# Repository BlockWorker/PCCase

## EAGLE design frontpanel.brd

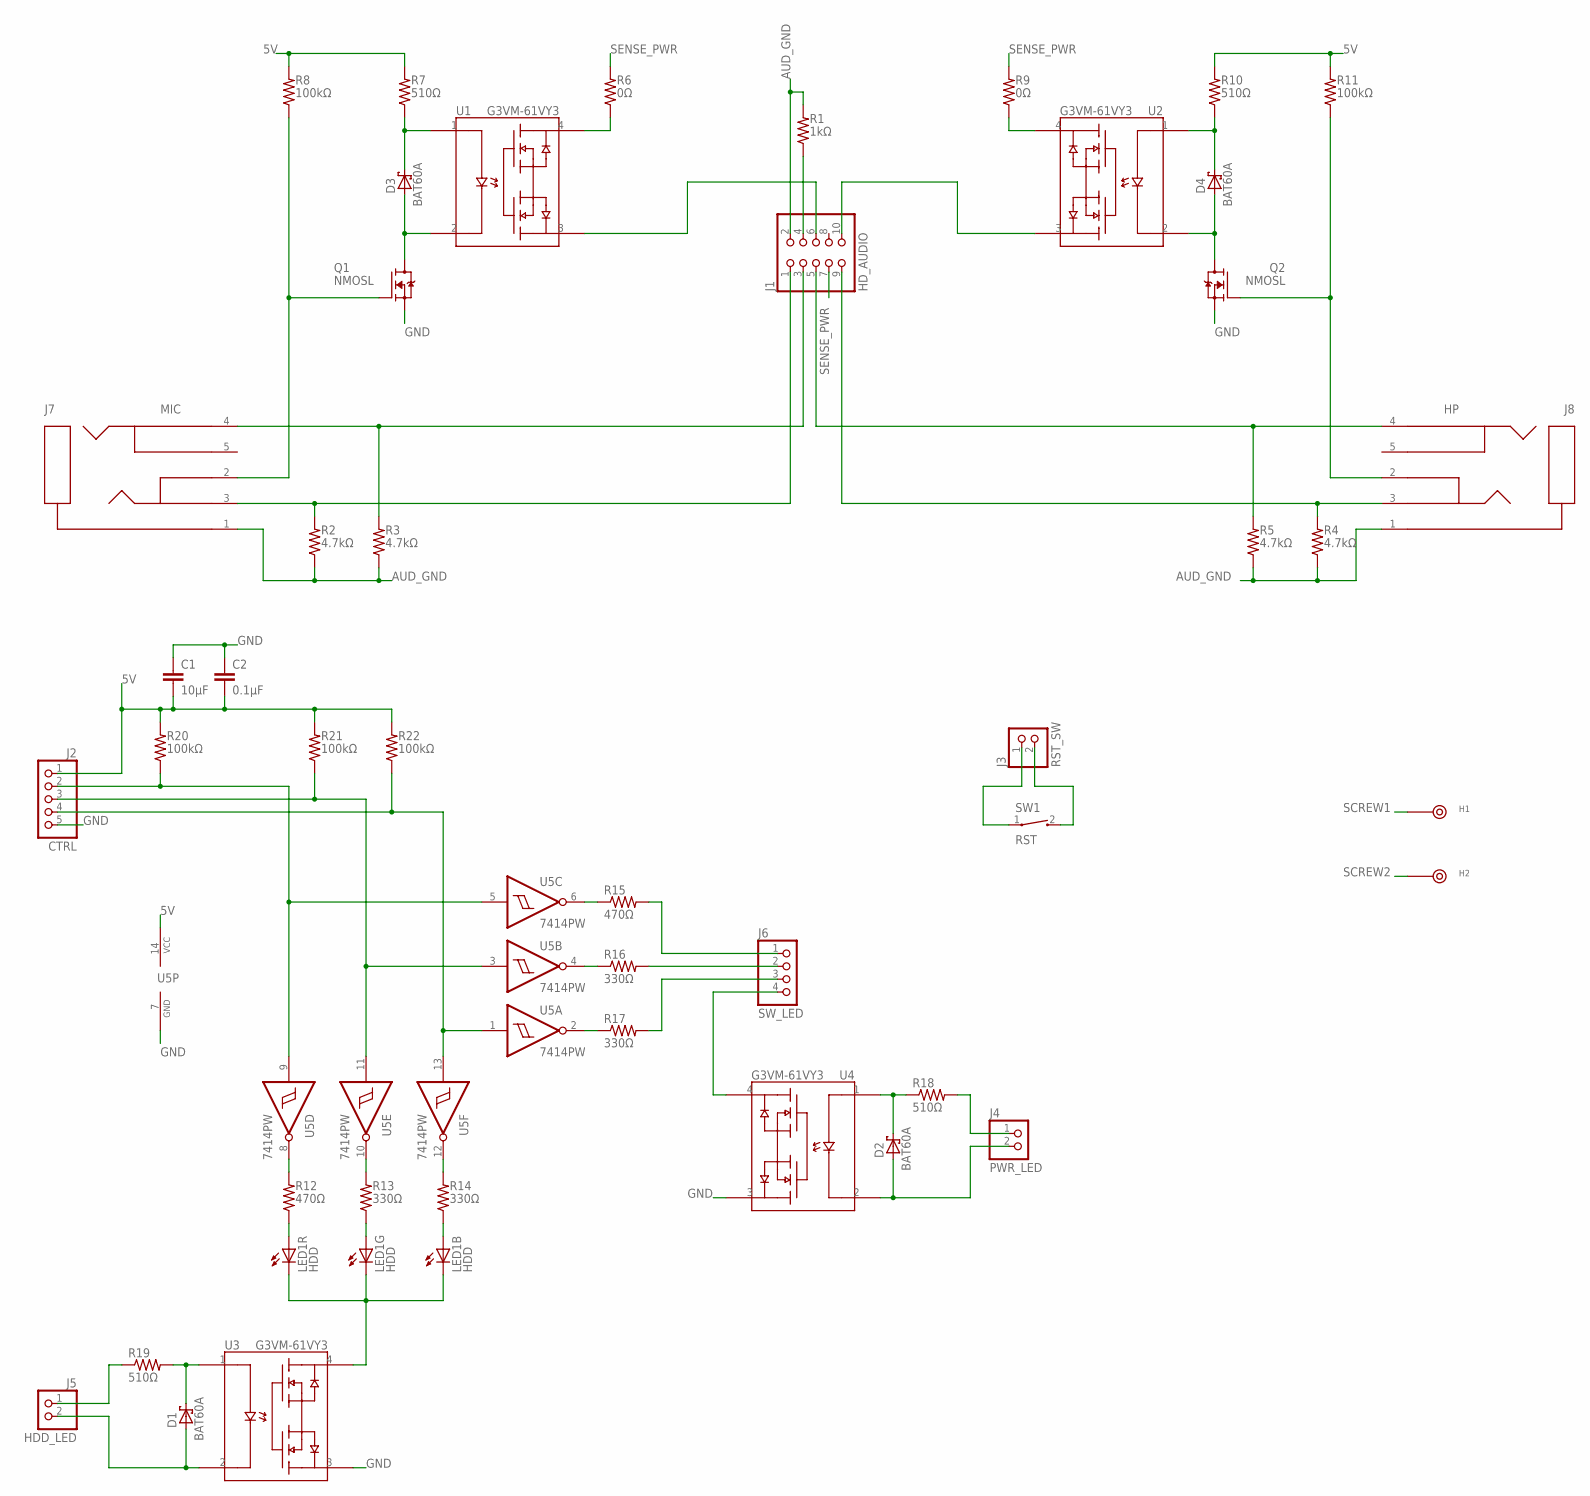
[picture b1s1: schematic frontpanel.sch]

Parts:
C1: 10µF; C0805
C2: 0.1µF; C0603
D1, D2, D3, D4: BAT60A; SOD323
H1, H2: 7466313R
J1: HD_AUDIO; 2X05
J2: CTRL; 1X05
J3: RST_SW; 1X02
J4: PWR_LED; 1X02
J5: HDD_LED; 1X02
J6: SW_LED; 1X04
J7: MIC; ACJS-MV35-5
J8: HP; ACJS-MV35-5
LED1: HDD; PLCC-6
Q1, Q2: NMOSL; SOT23
R1: 1kΩ; R0603
R2, R3, R4, R5: 4.7kΩ; R0603
R6, R9: 0Ω; R0603
R7, R10, R18, R19: 510Ω; R0603
R8, R11, R20, R21, R22: 100kΩ; R0603
R12, R15: 470Ω; R0603
R13, R14, R16, R17: 330Ω; R0603
SW1: RST; TLS-*J-LFS
U1, U2, U3, U4: G3VM-61VY3; SOP-4
U5: 7414PW; TSSOP14

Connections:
5V: C1.2, C2.2, J2.1, R7.2, R8.2, R10.2, R11.2, R20.2, R21.2, R22.2, U5.14 (VCC)
!PWM_B: J2.4, R22.1, U5.1 (I), U5.13 (I)
!PWM_G: J2.3, R21.1, U5.3 (I), U5.11 (I)
!PWM_R: J2.2, R20.1, U5.5 (I), U5.9 (I)
AUD_GND: J1.2, J7.1 (S), J8.1 (S), R1.2, R2.1, R3.1, R4.1, R5.1
GND: C1.1, C2.1, J2.5, Q1.2 (S), Q2.2 (S), U3.3 (1), U4.3 (1), U5.7 (GND)
HDD_LED_B: LED1.5 (A), R14.1
HDD_LED_B_RAW: R14.2, U5.12 (O)
HDD_LED_DRIVE: D1.1 (C), R19.2, U3.1 (A)
HDD_LED_G: LED1.3 (A), R13.1
HDD_LED_G_RAW: R13.2, U5.10 (O)
HDD_LED_IN+: J5.1, R19.1
HDD_LED_IN-: D1.2 (A), J5.2, U3.2 (K)
HDD_LED_K: LED1.2 (C), LED1.4 (C), LED1.6 (C), U3.4 (2)
HDD_LED_R: LED1.1 (A), R12.1
HDD_LED_R_RAW: R12.2, U5.8 (O)
HEADER_SENSE: J1.4, R1.1
HP_L: J1.9, J8.3 (T), R4.2
HP_R: J1.5, J8.4 (R), R5.2
HP_SENSE: J1.10, U2.3 (1)
HP_SENSEDR_A: D4.1 (C), R10.1, U2.1 (A)
HP_SENSEDR_K: D4.2 (A), Q2.3 (D), U2.2 (K)
HP_SENSE_PWR: R9.1, U2.4 (2)
HP_TIPSW: J8.2 (T-RETURN), Q2.1 (G), R11.1
MIC_L: J1.1, J7.3 (T), R2.2
MIC_R: J1.3, J7.4 (R), R3.2
MIC_SENSE: J1.6, U1.3 (1)
MIC_SENSEDR_A: D3.1 (C), R7.1, U1.1 (A)
MIC_SENSEDR_K: D3.2 (A), Q1.3 (D), U1.2 (K)
MIC_SENSE_PWR: R6.1, U1.4 (2)
MIC_TIPSW: J7.2 (T-RETURN), Q1.1 (G), R8.1
PWR_LED_IN+: J4.1, R18.2
PWR_LED_IN-: D2.2 (A), J4.2, U4.2 (K)
RST_SW_1: J3.1, SW1.1
RST_SW_2: J3.2, SW1.2
SCREW1: H1.H1, H1.H2, H1.P
SCREW2: H2.H1, H2.H2, H2.P
SENSE_PWR: J1.7, R6.2, R9.2
SW_LED_B: J6.3, R17.2
SW_LED_B_RAW: R17.1, U5.2 (O)
SW_LED_DRIVE: D2.1 (C), R18.1, U4.1 (A)
SW_LED_G: J6.2, R16.2
SW_LED_G_RAW: R16.1, U5.4 (O)
SW_LED_K: J6.4, U4.4 (2)
SW_LED_R: J6.1, R15.2
SW_LED_R_RAW: R15.1, U5.6 (O)

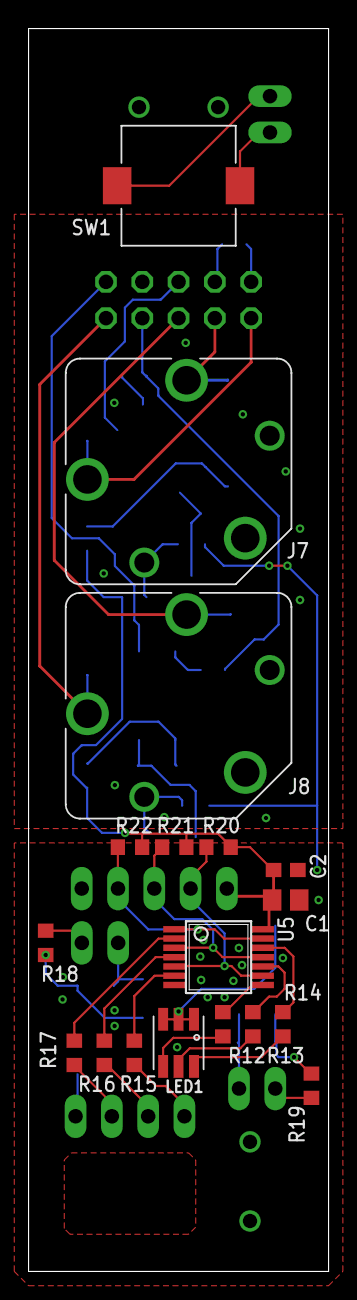
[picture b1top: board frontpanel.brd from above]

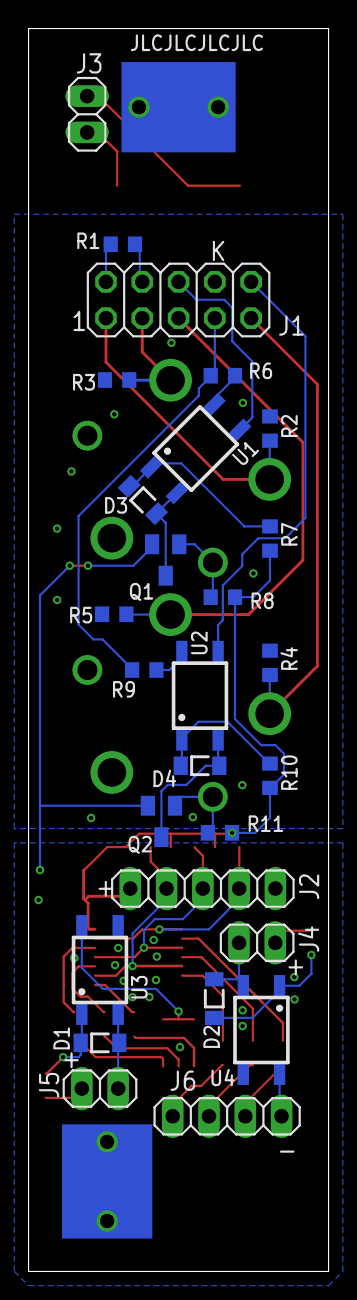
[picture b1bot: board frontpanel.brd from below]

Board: 2 copper layers, 21.0 x 87.0 mm, 47 parts (29 on the bottom side), 46 nets.

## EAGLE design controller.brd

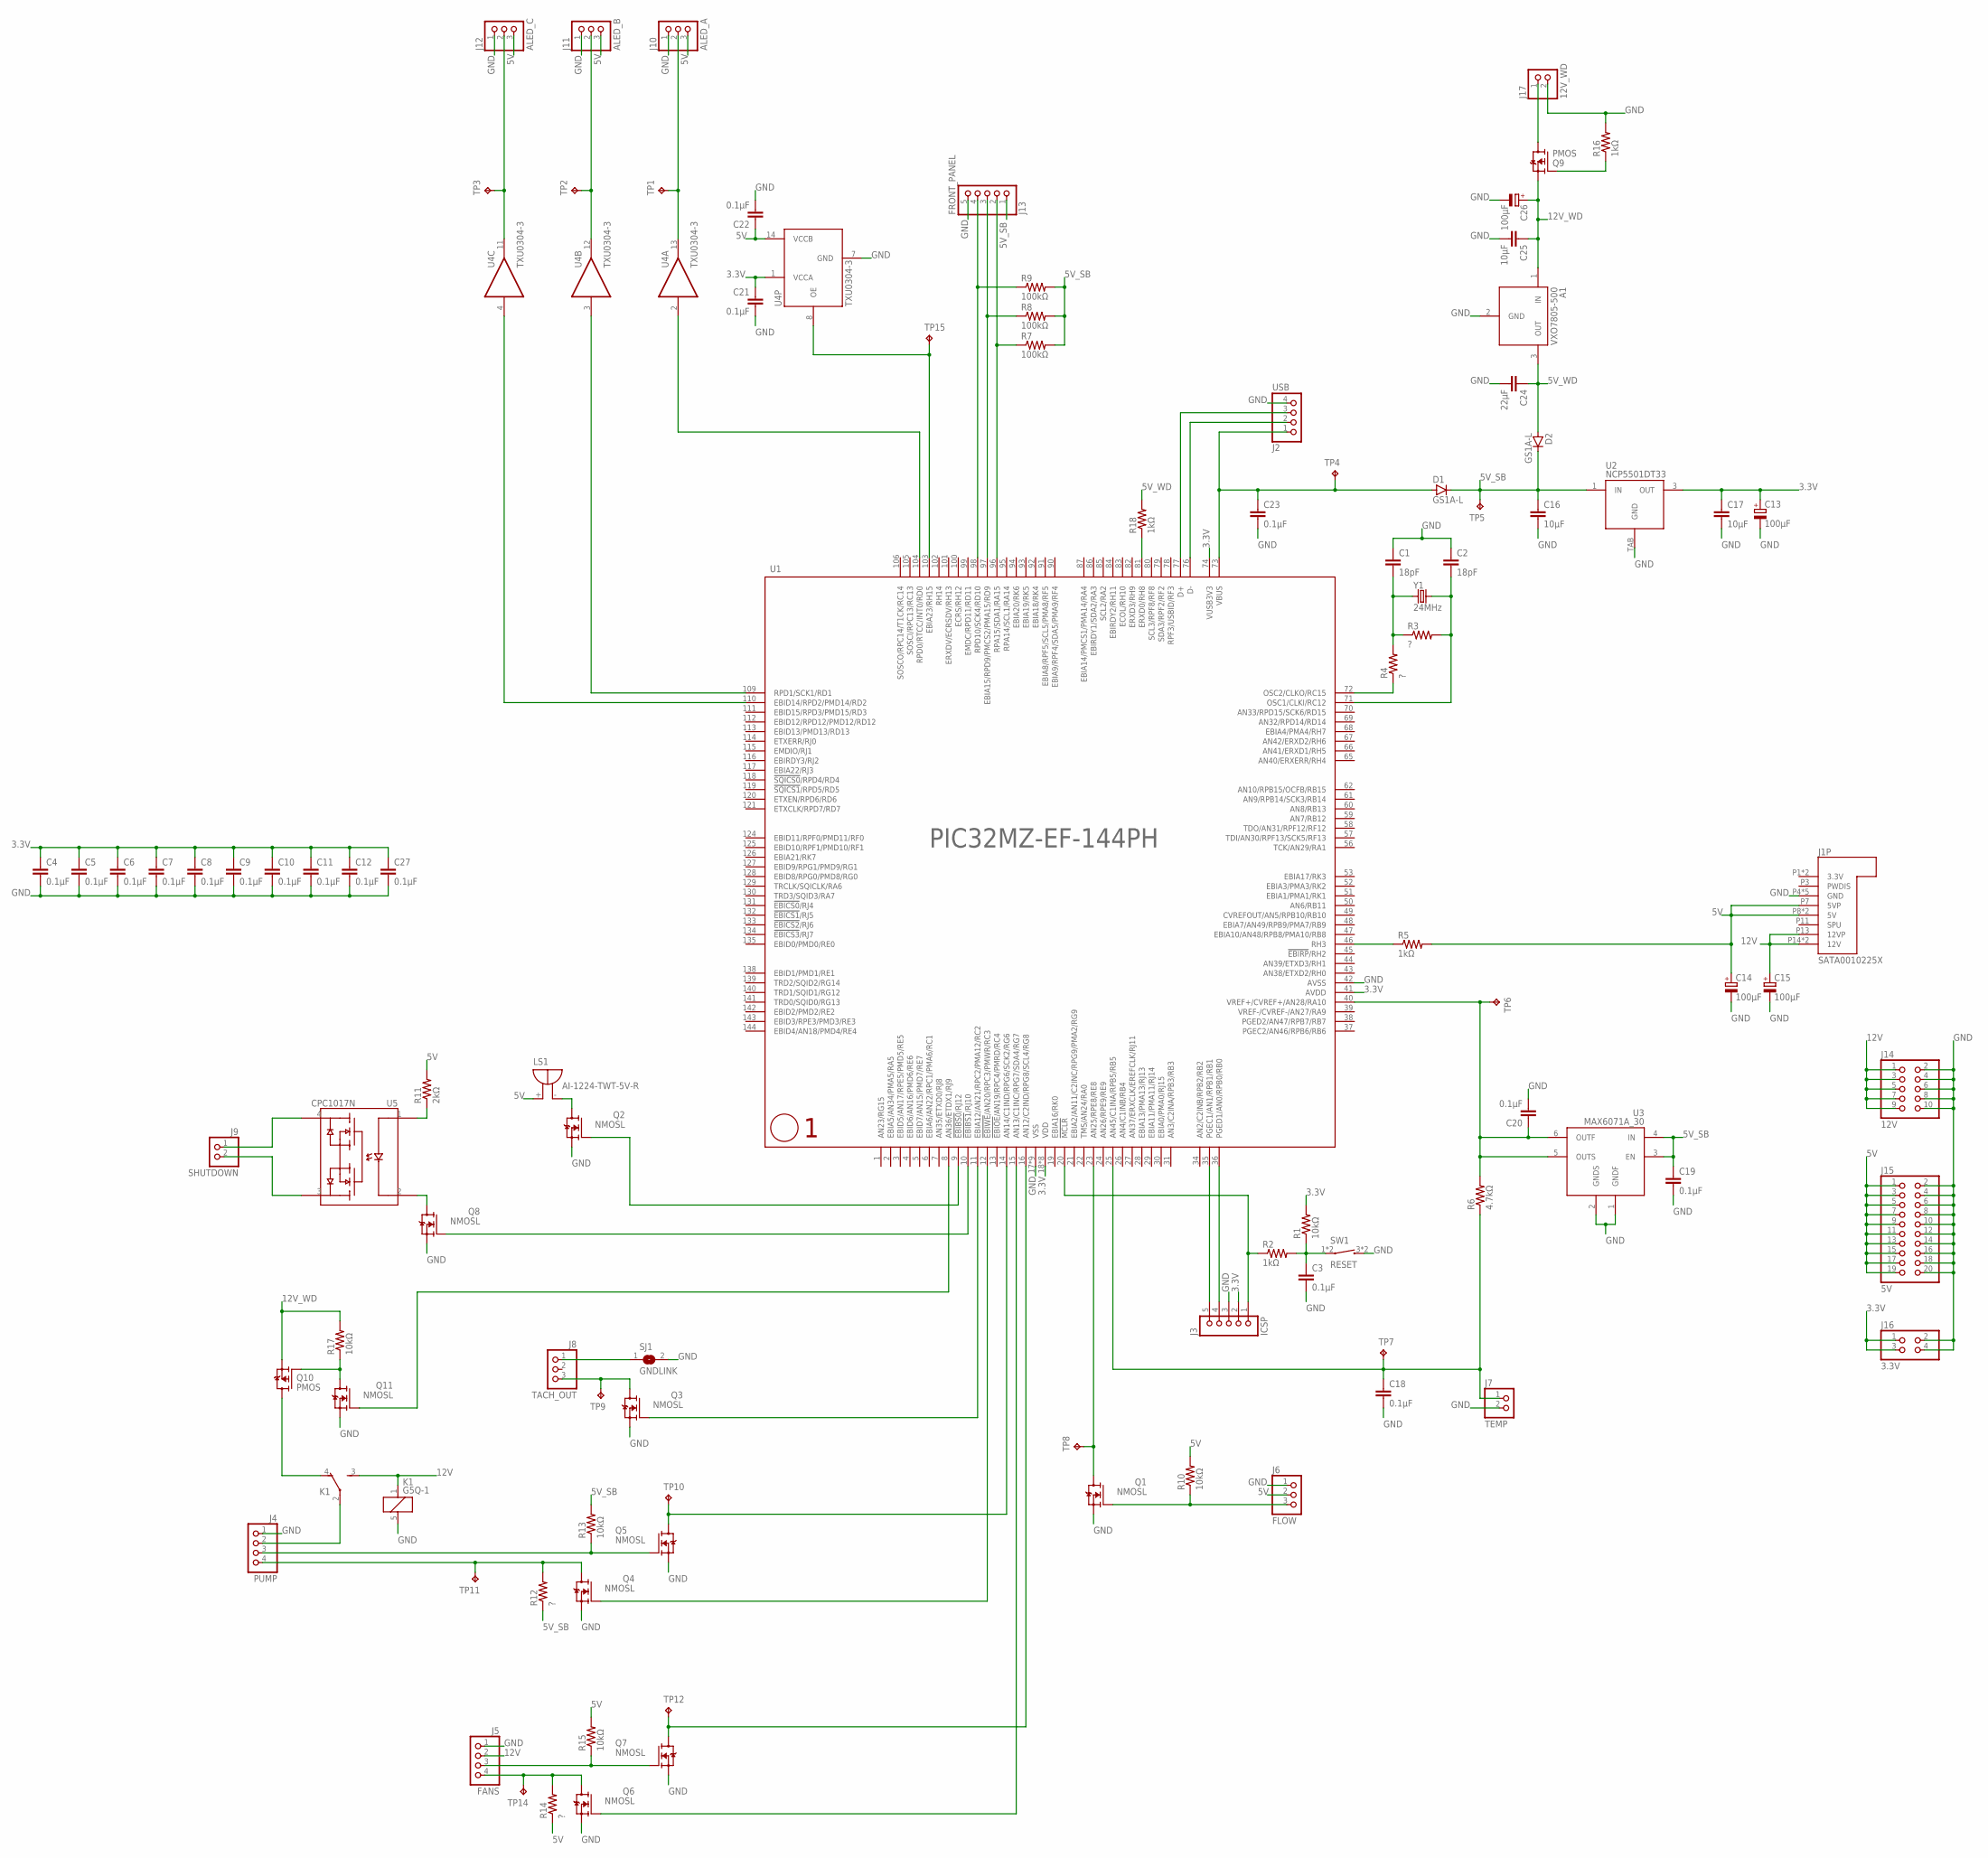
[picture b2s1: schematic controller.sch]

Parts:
A1: VXO7805-500; VXO78-500
C1, C2: 18pF; C0603
C3, C4, C5, C6, C7, C8, C9, C10, C11, C12, C18, C19, C20, C21, C22, C23, C27: 0.1µF; C0603
C13, C14, C15, C26: 100µF; PANASONIC_D
C16, C17, C25: 10µF; C0805
C24: 22µF; C0603
D1, D2: GS1A-L; DO-214AC
J1: SATA0010225X
J2: USB; 1X04
J3: ICSP; 5PIN-1.27
J4: PUMP; 47053-1000
J5: FANS; 47053-1000
J6: FLOW; 22-23-2032
J7: TEMP; 1X02
J8: TACH_OUT; 22-23-2032
J9: SHUTDOWN; 1X02
J10: ALED_A; B3B-XH-A
J11: ALED_B; B3B-XH-A
J12: ALED_C; B3B-XH-A
J13: FRONT_PANEL; 1X05
J14: 12V; 2X05
J15: 5V; 2X10
J16: 3.3V; 2X02
J17: 12V_WD; 1X02
K1: G5Q-1
LS1: AI-1224-TWT-5V-R
Q1, Q2, Q3, Q4, Q5, Q6, Q7, Q8, Q11: NMOSL; SOT23
Q9, Q10: PMOS; SOT23
R1, R10, R13, R15, R17: 10kΩ; R0603
R2, R5, R16, R18: 1kΩ; R0603
R3, R4, R12, R14: ?; R0603
R6: 4.7kΩ; R0603
R7, R8, R9: 100kΩ; R0603
R11: 2kΩ; R0603
SJ1: GNDLINK; SJ
SW1: RESET; TL3305_MICROSWITCH
TP1, TP2, TP3, TP4, TP5, TP6, TP7, TP8, TP9, TP10, TP11, TP12, TP14, TP15: RCU-0(J); TP_0603_JOINED
U1: PIC32MZ-EF-144PH; TQFP144-16X16
U2: NCP5501DT33; DPAK
U3: MAX6071A_30; SOT23-6L
U4: TXU0304-3; TSSOP14
U5: CPC1017N; CPC10*N
Y1: 24MHz; HC49/4HSMX

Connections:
3.3V: C4.1, C5.1, C6.1, C7.1, C8.1, C9.1, C10.1, C11.1, C12.1, C13.+, C17.1, C21.1, C27.1, J3.2, J16.1, J16.3, R1.2, U1.18 (VDD), U1.33 (VDD), U1.41 (AVDD), U1.55 (VDD), U1.64 (VDD), U1.74 (VUSB3V3), U1.88 (VDD), U1.107 (VDD), U1.122 (VDD), U1.137 (VDD), U2.3 (OUT), U4.1 (VCCA)
3V_REF: C20.1, R6.2, TP6.1, U1.40 (VREF+/CVREF+/AN28/RA10), U3.5 (OUTS), U3.6 (OUTF)
5V: C14.+, C22.1, J1.P7 (5VP), J1.P8 (5V), J1.P9 (5V), J6.2, J10.3, J11.3, J12.3, J15.1, J15.3, J15.5, J15.7, J15.9, J15.11, J15.13, J15.15, J15.17, J15.19, LS1.+, R5.2, R10.2, R11.2, R14.1, R15.2, U4.14 (VCCB)
5V_SB: C16.1, C19.1, D1.C, D2.C, J13.1, R7.2, R8.2, R9.2, R12.1, R13.2, TP5.1, U2.1 (IN), U3.3 (EN), U3.4 (IN)
5V_USB: C23.1, D1.A, J2.1, TP4.1, U1.73 (VBUS)
5V_WD: A1.3 (OUT), C24.1, D2.A, R18.2
12V: C15.+, J1.P13 (12VP), J1.P14 (12V), J1.P15 (12V), J5.2, J14.1, J14.3, J14.5, J14.7, J14.9, K1.1, K1.3 (S)
12V_PUMP: J4.2, K1.2
12V_PUMP_WD: K1.4 (O), Q10.3 (D)
12V_WD: A1.1 (IN), C25.1, C26.+, Q9.2 (S), Q10.2 (S), R17.2
12V_WD_PROTECT: Q9.1 (G), R16.1
12V_WD_RAW: J17.1, Q9.3 (D)
!MCLR: J3.1, R2.1, U1.20 (!MCLR)
!MCLR!_FILTER: C3.1, R1.1, R2.2, SW1.1, SW1.2 (1)
ALED_A: J10.2, TP1.1, U4.13 (O)
ALED_A_RAW: U1.104 (RPD0/RTCC/INT0/RD0), U4.2 (I)
ALED_B: J11.2, TP2.1, U4.12 (O)
ALED_B_RAW: U1.109 (RPD1/SCK1/RD1), U4.3 (I)
ALED_C: J12.2, TP3.1, U4.11 (O)
ALED_C_RAW: U1.110 (EBID14/RPD2/PMD14/RD2), U4.4 (I)
ALED_OE: TP15.1, U1.103 (EBIA23/RH15), U4.8 (OE)
BUZZER_EN: Q2.1 (G), U1.9 (!EBIBS0!/RJ12)
BUZZER_L: LS1.-, Q2.3 (D)
EMERGENCY_SD_C1: J9.1, U5.4 (2)
EMERGENCY_SD_C2: J9.2, U5.3 (1)
EMERGENCY_SD_DRIVE+: R11.1, U5.1 (A)
EMERGENCY_SD_DRIVE-: Q8.3 (D), U5.2 (K)
EMERGENCY_SD_TRIGGER: Q8.1 (G), U1.10 (!EBIBS1!/RJ10)
FAN_PWM: J5.4, Q6.3 (D), R14.2, TP14.1
FAN_PWM_DRIVE: Q6.1 (G), U1.15 (AN13/C1INC/RPG7/SDA4/RG7)
FAN_TACH: Q7.3 (D), TP12.1, U1.16 (AN12/C2IND/RPG8/SCL4/RG8)
FAN_TACH_RAW: J5.3, Q7.1 (G), R15.1
FLOW_TACH: Q1.3 (D), TP8.1, U1.23 (AN25/RPE8/RE8)
FLOW_TACH_RAW: J6.3, Q1.1 (G), R10.1
FPLED_!B: J13.4, R9.1, U1.98 (RPD10/SCK4/RD10)
FPLED_!G: J13.3, R8.1, U1.97 (EBIA15/RPD9/PMCS2/PMA15/RD9)
FPLED_!R: J13.2, R7.1, U1.96 (RPA15/SDA1/RA15)
GND: A1.2 (GND), C1.1, C2.1, C3.2, C4.2, C5.2, C6.2, C7.2, C8.2, C9.2, C10.2, C11.2, C12.2, C13.-, C14.-, C15.-, C16.2, C17.2, C18.2, C19.2, C20.2, C21.2, C22.2, C23.2, C24.2, C25.2, C26.-, C27.2, J1.P4 (GND), J1.P5 (GND), J1.P6 (GND), J1.P10 (GND), J1.P12 (GND), J2.4, J3.3, J4.1, J5.1, J6.1, J7.2, J10.1, J11.1, J12.1, J13.5, J14.2, J14.4, J14.6, J14.8, J14.10, J15.2, J15.4, J15.6, J15.8, J15.10, J15.12, J15.14, J15.16, J15.18, J15.20, J16.2, J16.4, J17.2, K1.5 (2), Q1.2 (S), Q2.2 (S), Q3.2 (S), Q4.2 (S), Q5.2 (S), Q6.2 (S), Q7.2 (S), Q8.2 (S), Q11.2 (S), R16.2, SJ1.2, SW1.3 (2), SW1.4 (2), U1.17 (VSS), U1.32 (VSS), U1.42 (AVSS), U1.54 (VSS), U1.63 (VSS), U1.75 (VSS), U1.89 (VSS), U1.108 (VSS), U1.123 (VSS), U1.136 (VSS), U2.TAB (GND), U3.1 (GNDF), U3.2 (GNDS), U4.7 (GND)
OSC1: C2.2, R3.2, U1.71 (OSC1/CLKI/RC12), Y1.2
OSC2: R4.1, U1.72 (OSC2/CLKO/RC15)
OSC2_R: C1.2, R3.1, R4.2, Y1.1
PGEC: J3.5, U1.35 (PGEC1/AN1/RPB1/RB1)
PGED: J3.4, U1.36 (PGED1/AN0/RPB0/RB0)
POWER_SENSE: R5.1, U1.46 (RH3)
PUMP_PWM: J4.4, Q4.3 (D), R12.2, TP11.1
PUMP_PWM_DRIVE: Q4.1 (G), U1.12 (!EBIWE!/AN20/RPC3/PMWR/RC3)
PUMP_TACH: Q5.3 (D), TP10.1, U1.14 (AN14/C1IND/RPG6/SCK2/RG6)
PUMP_TACH_RAW: J4.3, Q5.1 (G), R13.1
PUMP_WD_DRIVE: Q10.1 (G), Q11.3 (D), R17.1
PUMP_WD_RUN: Q11.1 (G), U1.8 (AN36/ETDX1/RJ9)
TACH_OUT: J8.3, Q3.3 (D), TP9.1
TACH_OUT_DRIVE: Q3.1 (G), U1.11 (EBIA12/AN21/RPC2/PMA12/RC2)
TACH_OUT_GNDLINK: J8.1, SJ1.1
TEMP_SENSE: C18.1, J7.1, R6.1, TP7.1, U1.25 (AN45/C1INA/RPB5/RB5)
USB_D+: J2.3, U1.77 (D+)
USB_D-: J2.2, U1.76 (D-)
WD_DETECT: R18.1, U1.81 (ERXD0/RH8)

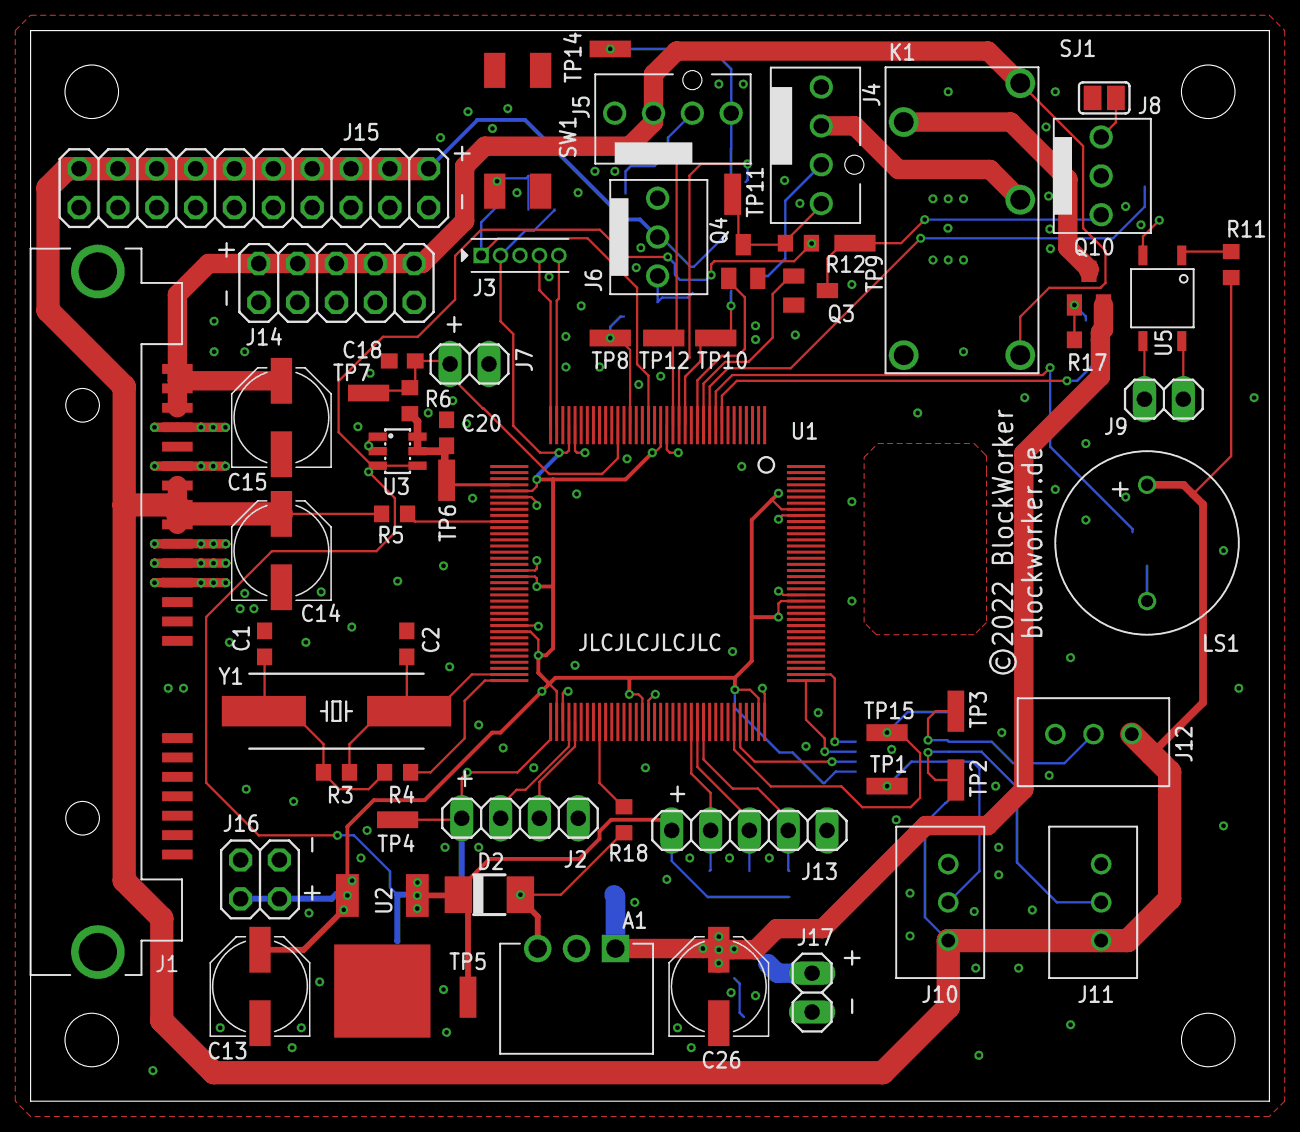
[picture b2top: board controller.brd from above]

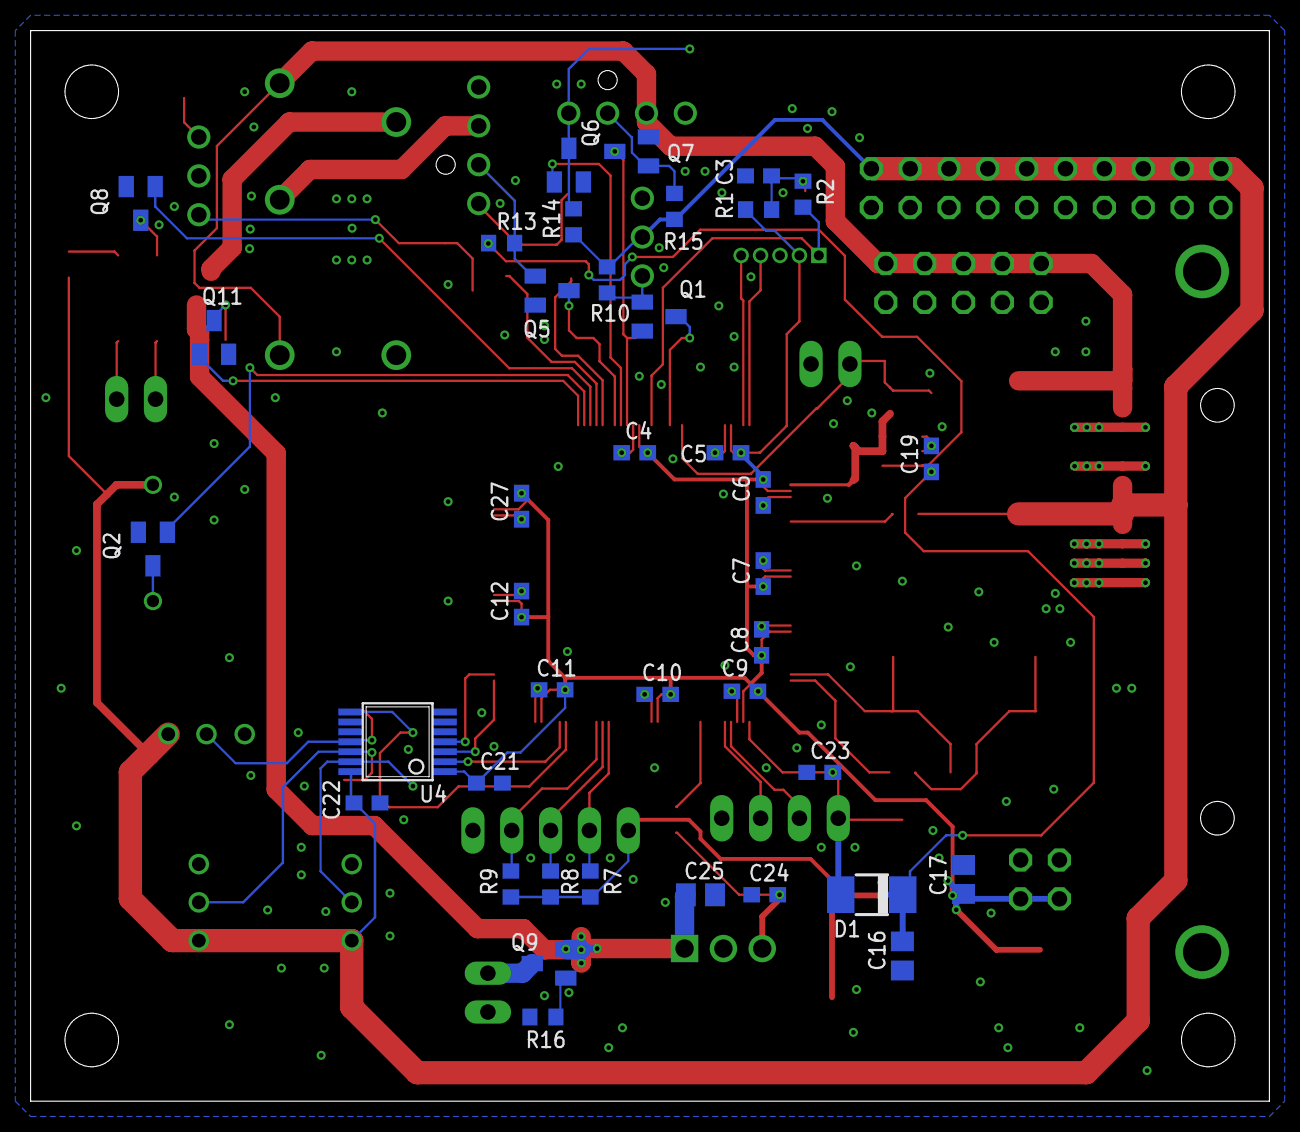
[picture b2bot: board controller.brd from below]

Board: 2 copper layers, 81.0 x 70.0 mm, 100 parts (39 on the bottom side), 57 nets.

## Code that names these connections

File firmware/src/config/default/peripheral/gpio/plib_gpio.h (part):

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// *****************************************************************************


/*** Macros for PUMP_WD_RUN pin ***/
#define PUMP_WD_RUN_Set()               (LATJSET = (1<<9))
#define PUMP_WD_RUN_Clear()             (LATJCLR = (1<<9))
#define PUMP_WD_RUN_Toggle()            (LATJINV= (1<<9))
#define PUMP_WD_RUN_OutputEnable()      (TRISJCLR = (1<<9))
#define PUMP_WD_RUN_InputEnable()       (TRISJSET = (1<<9))
#define PUMP_WD_RUN_Get()               ((PORTJ >> 9) & 0x1)
#define PUMP_WD_RUN_PIN                  GPIO_PIN_RJ9

/*** Macros for BUZZER pin ***/
#define BUZZER_Set()               (LATJSET = (1<<12))
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#define EMERGENCY_SD_Get()               ((PORTJ >> 10) & 0x1)
#define EMERGENCY_SD_PIN                  GPIO_PIN_RJ10

/*** Macros for TACH_OUT pin ***/
#define TACH_OUT_Get()               ((PORTC >> 2) & 0x1)
#define TACH_OUT_PIN                  GPIO_PIN_RC2

/*** Macros for PUMP_PWM pin ***/
#define PUMP_PWM_Get()               ((PORTC >> 3) & 0x1)
#define PUMP_PWM_PIN                  GPIO_PIN_RC3

/*** Macros for PUMP_TACH pin ***/
#define PUMP_TACH_Get()               ((PORTG >> 6) & 0x1)
#define PUMP_TACH_PIN                  GPIO_PIN_RG6

/*** Macros for FAN_PWM pin ***/
#define FAN_PWM_Get()               ((PORTG >> 7) & 0x1)
#define FAN_PWM_PIN                  GPIO_PIN_RG7

/*** Macros for FAN_TACH pin ***/
#define FAN_TACH_Get()               ((PORTG >> 8) & 0x1)
#define FAN_TACH_PIN                  GPIO_PIN_RG8

/*** Macros for FLOW_TACH pin ***/
#define FLOW_TACH_Get()               ((PORTE >> 8) & 0x1)
#define FLOW_TACH_PIN                  GPIO_PIN_RE8

/*** Macros for WATER_TEMP pin ***/
#define WATER_TEMP_Get()               ((PORTB >> 5) & 0x1)
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#define PWR_DETECT_InterruptEnable()   (CNENHSET = (1<<3))
#define PWR_DETECT_InterruptDisable()  (CNENHCLR = (1<<3))

/*** Macros for WD_DETECT pin ***/
#define WD_DETECT_Set()               (LATHSET = (1<<8))
#define WD_DETECT_Clear()             (LATHCLR = (1<<8))
#define WD_DETECT_Toggle()            (LATHINV= (1<<8))
#define WD_DETECT_OutputEnable()      (TRISHCLR = (1<<8))
#define WD_DETECT_InputEnable()       (TRISHSET = (1<<8))
#define WD_DETECT_Get()               ((PORTH >> 8) & 0x1)
#define WD_DETECT_PIN                  GPIO_PIN_RH8
#define WD_DETECT_InterruptEnable()   (CNENHSET = (1<<8))
#define WD_DETECT_InterruptDisable()  (CNENHCLR = (1<<8))

/*** Macros for FPLED_R pin ***/
#define FPLED_R_Get()               ((PORTA >> 15) & 0x1)
#define FPLED_R_PIN                  GPIO_PIN_RA15

/*** Macros for FPLED_G pin ***/
#define FPLED_G_Get()               ((PORTD >> 9) & 0x1)
#define FPLED_G_PIN                  GPIO_PIN_RD9

/*** Macros for FPLED_B pin ***/
#define FPLED_B_Get()               ((PORTD >> 10) & 0x1)
#define FPLED_B_PIN                  GPIO_PIN_RD10

/*** Macros for ALED_OE pin ***/
#define ALED_OE_Set()               (LATHSET = (1<<15))
#define ALED_OE_Clear()             (LATHCLR = (1<<15))
#define ALED_OE_Toggle()            (LATHINV= (1<<15))
#define ALED_OE_OutputEnable()      (TRISHCLR = (1<<15))
#define ALED_OE_InputEnable()       (TRISHSET = (1<<15))
#define ALED_OE_Get()               ((PORTH >> 15) & 0x1)
#define ALED_OE_PIN                  GPIO_PIN_RH15

/*** Macros for ALED_A_DATA pin ***/
#define ALED_A_DATA_Get()               ((PORTD >> 0) & 0x1)
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
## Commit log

2022-02-09 Initial commit.
2022-02-11 Firmware added, controller progress
2022-02-18 Controller (hopefully) finished
2022-02-27 Parts Ordered
2022-03-13 Replaced MCU footprint due to earlier error
2022-04-02 Electronics assembled, ARGB controller done
2022-04-12 Controller programming mostly complete
2022-04-16 Controller (semi-)finished
2022-04-17 Added pump control test
2022-04-18 Weirdness.
2022-04-20 Enabled WDT
2022-11-19 minor stuff
2022-11-20 Minor changes to watchdog and acceptable vals
2023-04-25 Miscellaneous progress
2023-04-25 New frontpanel fixes
2023-06-09 CaseControl rework and progress
2024-01-15 updated and LFS

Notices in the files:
firmware/src/config/default/peripheral/gpio/plib_gpio.h:
Copyright (C) 2019 Microchip Technology Inc. and its subsidiaries.
controller.brd:
©2022 BlockWorker
